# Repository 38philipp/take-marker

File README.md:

# Take-Marker

Bauzeichnung, Platine, Test-Suite und Auswertung für den Take-Marker, ein Gerät auf dem Blitzschuh der Kamera. Projektunterricht 2026/27.

Online: https://38philipp.github.io/take-marker/

- `docs/` ist die Website (GitHub Pages, Branch main, Ordner docs).
- `bin/build.py` baut `docs/` neu aus den Quelldateien.
- Die Test-Suite braucht Chrome oder Edge (Web Serial) und das Gerät per USB.

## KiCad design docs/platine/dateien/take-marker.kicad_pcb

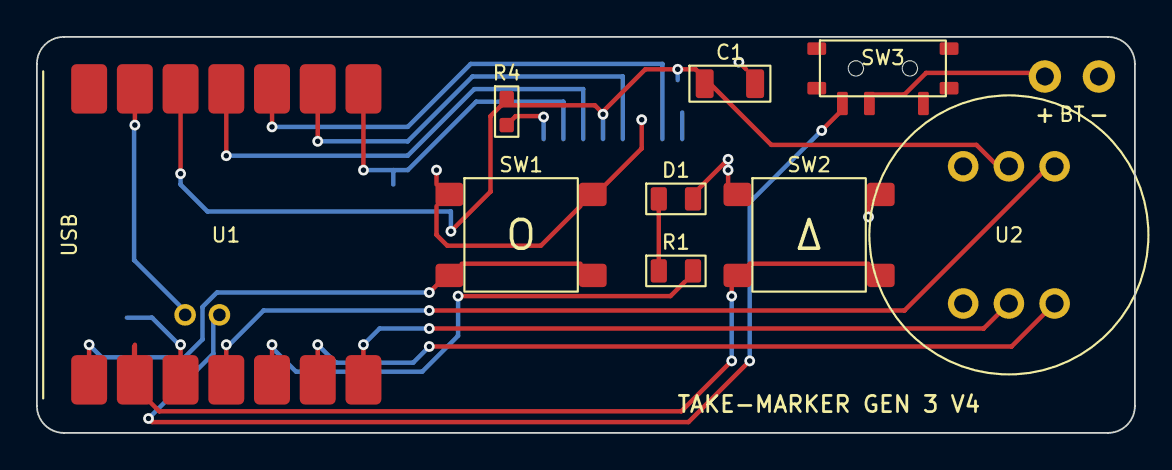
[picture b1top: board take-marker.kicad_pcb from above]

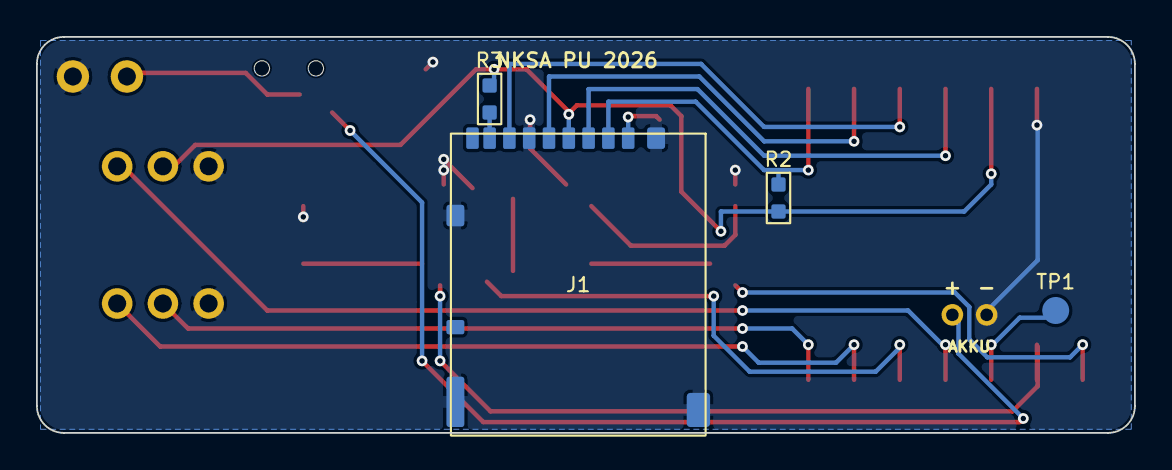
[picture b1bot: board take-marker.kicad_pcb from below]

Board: 2 copper layers, 61.0 x 22.0 mm, 14 parts (4 on the bottom side), 18 nets.

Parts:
BT: Akku 602050; BT
C1: 100uF 1206; C1
D1: LED 0805; D1
J1: Hirose DM3AT-SF-PEJM5; J1
R1: 330R 0805; R1
R2: 10k 0603; R2
R3: 10k 0603; R3
R4: 10k 0603; R4
SW1: PTS645SM43SMTR92 Marke; SW1
SW2: PTS645SM43SMTR92 Notiz; SW2
SW3: MSK12C02; SW3
TP1: Testpunkt D2; TP1
U1: XIAO ESP32-S3; U1
U2: DFRobot SEN0327; U2

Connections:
+3V3: C1.+, J1.4, R2.2, R3.2, R4.1, U1.3V3, U2.VDD
BATT+: BT.+, SW3.2
BTN_MARK: SW1.2, U1.D0
BTN_NOTE: SW2.2, U1.D1
GND: BT.-, C1.-, D1.K, J1.6, J1.SH, SW1.1, SW2.1, U1.BAT-, U1.GND, U2.GND, U2.L/R
LED_A: D1.A, R1.2
LED_D4: R1.1, U1.D4
MIC_SCK: U1.D5, U2.SCK
MIC_SD: U1.D3, U2.SD
MIC_WS: U1.D6, U2.WS
SD_CLK: J1.5, U1.D8
SD_CMD: J1.3, U1.D10
SD_CS: J1.2, R2.1, U1.D7
SD_DAT0: J1.7, U1.D9
SD_DAT1: J1.8, R3.1
SD_DAT2: J1.1, R4.2
TP_D2: TP1.D2, U1.D2
VBAT_SW: SW3.3, U1.BAT+
